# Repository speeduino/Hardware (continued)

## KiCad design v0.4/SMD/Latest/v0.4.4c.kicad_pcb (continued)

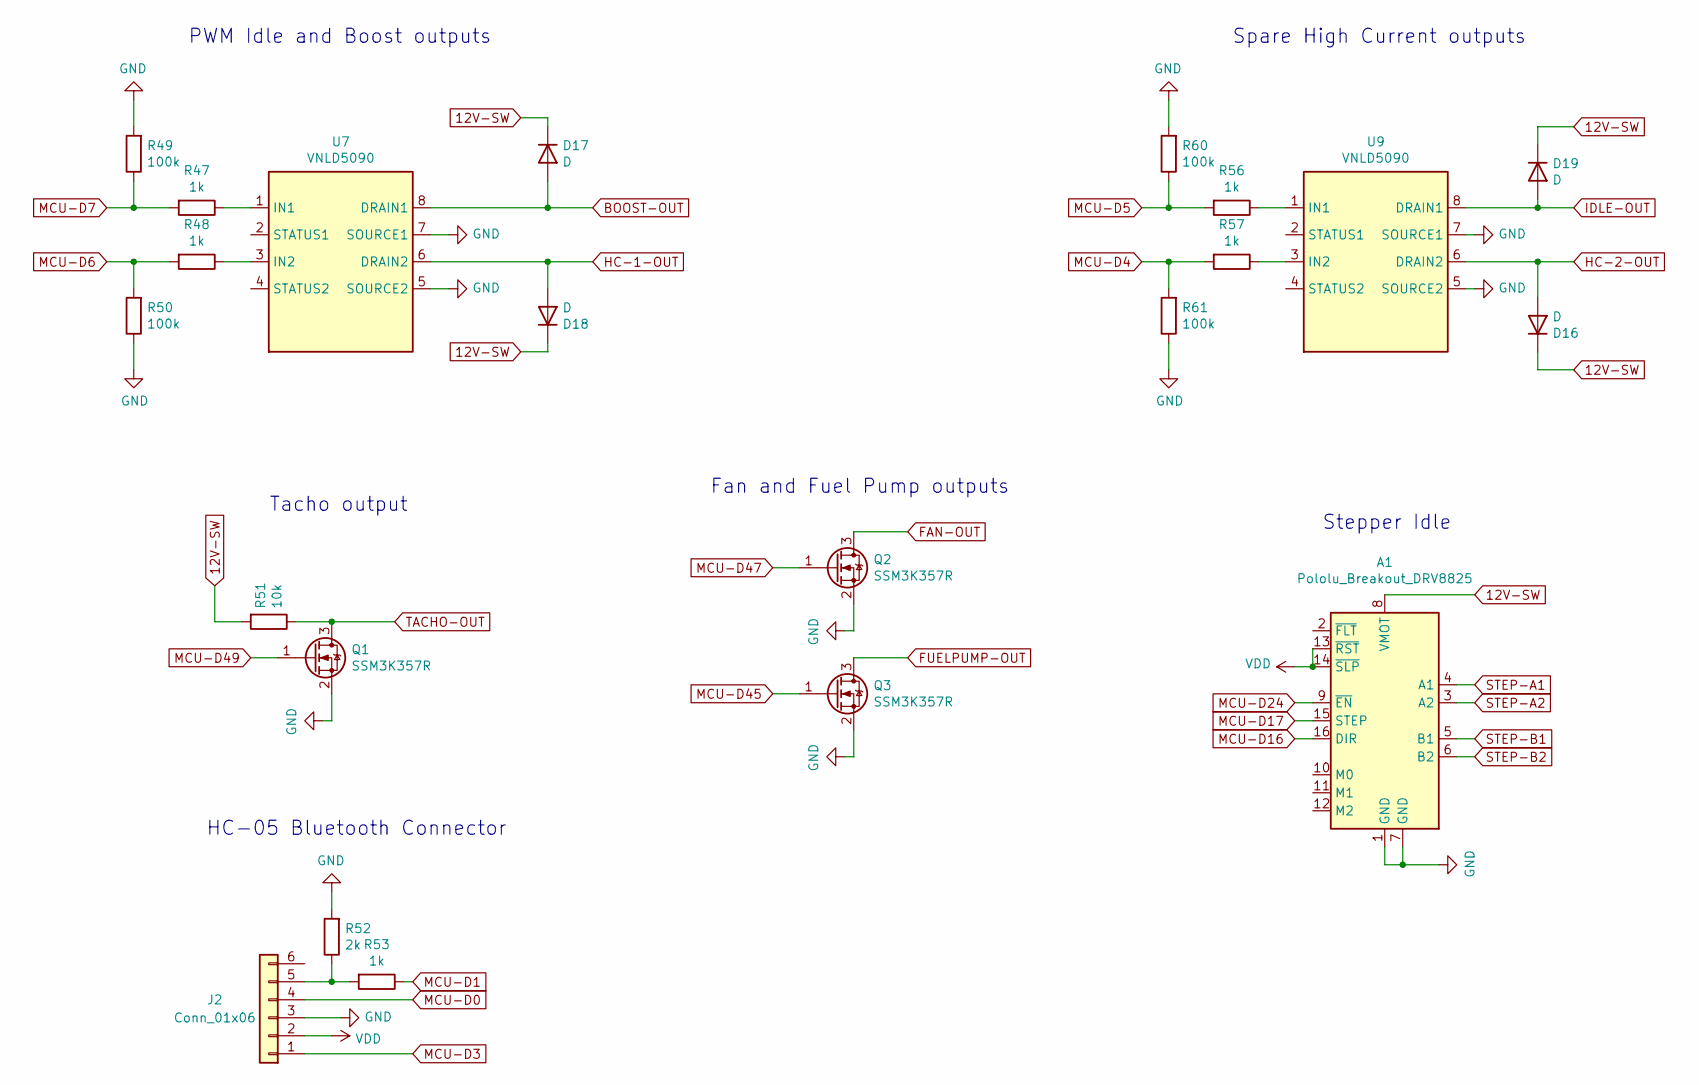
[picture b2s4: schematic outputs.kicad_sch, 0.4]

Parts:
A1: Pololu_Breakout_DRV8825; Pololu_Breakout-16_15.2x20.3mm
D16, D17, D18, D19: D; D_SOD-123F; Manufacturer_Part_Number S110FA; Digikey Part Number S110FACT-ND
J2: Conn_01x06; PinHeader_1x06_P2.54mm_Vertical
Q1, Q2, Q3: SSM3K357R; SOT-23; Manufacturer_Part_Number SSM3K357R; Digikey Part Number SSM3K357RLFCT-ND
R47, R48, R53, R56, R57: 1k; R_0805_2012Metric; Manufacturer_Part_Number RC0805FR-071KL; Digikey Part Number 311-1.00KCRCT-ND
R49, R50, R60, R61: 100k; R_0805_2012Metric; Manufacturer_Part_Number RC0805FR-07100KL; Digikey Part Number 311-100KCRCT-ND
R51: 10k; R_0805_2012Metric; Manufacturer_Part_Number RC0805JR-0710KL; Digikey Part Number 311-10KARCT-ND
R52: 2k; R_0805_2012Metric; Manufacturer_Part_Number RC0805FR-072KL; Digikey Part Number 311-2.00KCRCT-ND
U7, U9: VNLD5090; SO-8_3.9x4.9mm_P1.27mm; Manufacturer_Part_Number VNLD5090-E; Digikey Part Number 497-18682-ND

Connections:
BOOST-OUT: D17.2 (A), U7.8 (DRAIN1); also elsewhere on the board
FAN-OUT: Q2.3 (D); also elsewhere on the board
FUELPUMP-OUT: Q3.3 (D); also elsewhere on the board
GND: A1.1 (GND), A1.7 (GND), J2.3, Q1.2 (S), Q2.2 (S), Q3.2 (S), R49.2, R50.1, R52.2, R60.2, R61.1, U7.5 (SOURCE2), U7.7 (SOURCE1), U9.5 (SOURCE2), U9.7 (SOURCE1); also elsewhere on the board
HC-1-OUT: D18.2 (A), U7.6 (DRAIN2); also elsewhere on the board
HC-2-OUT: D16.2 (A), U9.6 (DRAIN2); also elsewhere on the board
IDLE-OUT: D19.2 (A), U9.8 (DRAIN1); also elsewhere on the board
MCU-D0: J2.4; also elsewhere on the board
MCU-D1: R53.1; also elsewhere on the board
MCU-D3: J2.1; also elsewhere on the board
MCU-D4: R57.2, R61.2; also elsewhere on the board
MCU-D5: R56.2, R60.1; also elsewhere on the board
MCU-D6: R48.2, R50.2; also elsewhere on the board
MCU-D7: R47.2, R49.1; also elsewhere on the board
MCU-D16: A1.16 (DIR); also elsewhere on the board
MCU-D17: A1.15 (STEP); also elsewhere on the board
MCU-D24: A1.9 (~EN); also elsewhere on the board
MCU-D45: Q3.1 (G); also elsewhere on the board
MCU-D47: Q2.1 (G); also elsewhere on the board
MCU-D49: Q1.1 (G); also elsewhere on the board
unnamed: J2.5, R52.1, R53.2
unnamed: R47.1, U7.1 (IN1)
unnamed: R48.1, U7.3 (IN2)
unnamed: R56.1, U9.1 (IN1)
unnamed: R57.1, U9.3 (IN2)
STEP-A1: A1.4 (A1); also elsewhere on the board
STEP-A2: A1.3 (A2); also elsewhere on the board
STEP-B1: A1.5 (B1); also elsewhere on the board
STEP-B2: A1.6 (B2); also elsewhere on the board
TACHO-OUT: Q1.3 (D), R51.1; also elsewhere on the board

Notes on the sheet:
Stepper Idle
HC-05 Bluetooth Connector
Spare High Current outputs
Fan and Fuel Pump outputs
PWM Idle and Boost outputs
Tacho output

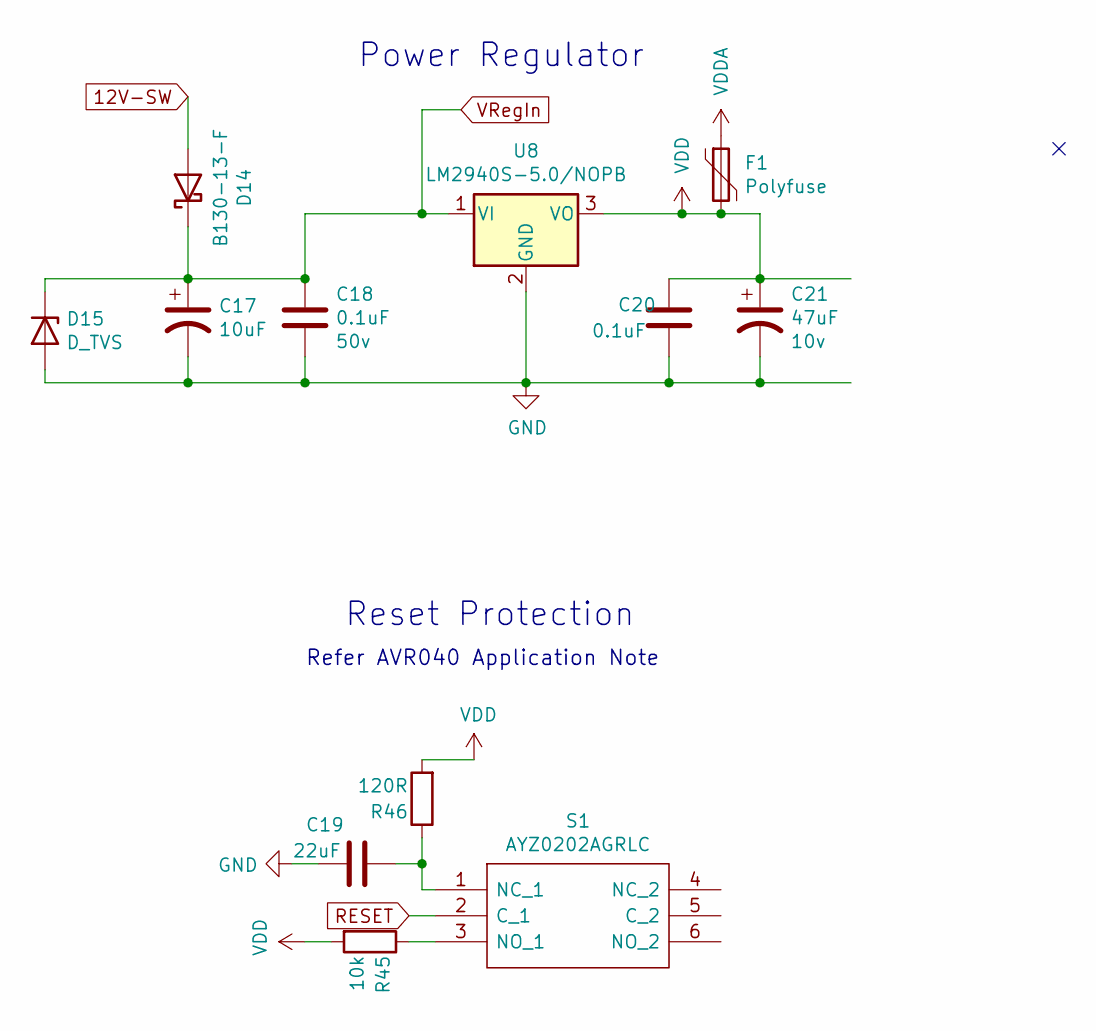
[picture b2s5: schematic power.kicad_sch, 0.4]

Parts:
C17: 10uF; CP_EIA-7343-31_Kemet-D; Voltage 35v; Manufacturer_Part_Number T491D106K050AT; Digikey Part Number 399-8361-1-ND
C18: 0.1uF; C_0805_2012Metric; Voltage 50v; Manufacturer_Part_Number CC0805KRX7R9BB104; Digikey Part Number 311-1140-1-ND
C19: 22uF; C_0805_2012Metric_Pad1.15x1.40mm_HandSolder; Manufacturer_Part_Number CL21A226KQCLRNC; Digikey Part Number 1276-6687-1-ND
C20: 0.1uF; C_0805_2012Metric; Manufacturer_Part_Number CC0805KRX7R9BB104; Digikey Part Number 311-1140-1-ND
C21: 47uF; CP_EIA-3528-21_Kemet-B; Voltage 10v; Manufacturer_Part_Number TAJB476K006RNJ; Digikey Part Number 478-1692-1-ND
D14: B130-13-F; D_SMA; Manufacturer_Part_Number B130-13-F; Digikey Part Number B130-FDICT-ND
D15: D_TVS; D_SMB; Manufacturer_Part_Number SMBJ40A-Q; Digikey Part Number SMBJ40A-QCT-ND
F1: Polyfuse; Fuse_1812_4532Metric; Manufacturer_Part_Number 0ZCC0050FF2C; Digikey Part Number 507-1361-1-ND
R45: 10k; R_0805_2012Metric; Manufacturer_Part_Number RC0805JR-0710KL; Digikey Part Number 311-10KARCT-ND
R46: 120R; R_0805_2012Metric; Manufacturer_Part_Number RC0805FR-07120RL; Digikey Part Number 311-120CRCT-ND
S1: AYZ0202AGRLC; Manufacturer_Part_Number AYZ0202AGRLC; Digikey Part Number 401-2013-1-ND
U8: LM2940S-5.0/NOPB; TO-263-3_TabPin2; Manufacturer_Part_Number LM2940S-5.0/NOPB; Digikey Part Number LM2940S-5.0/NOPB-ND

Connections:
GND: C17.2, C18.2, C19.2, C20.2, C21.2, D15.2 (A), U8.2 (GND); also elsewhere on the board
unnamed: C19.1, R46.1, S1.1 (NC_1)
unnamed: R45.1, S1.3 (NO_1)
RESET: S1.2 (C_1); also elsewhere on the board
VDDA: F1.1; also elsewhere on the board

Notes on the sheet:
Refer AVR040 Application Note
Reset Protection
Power Regulator

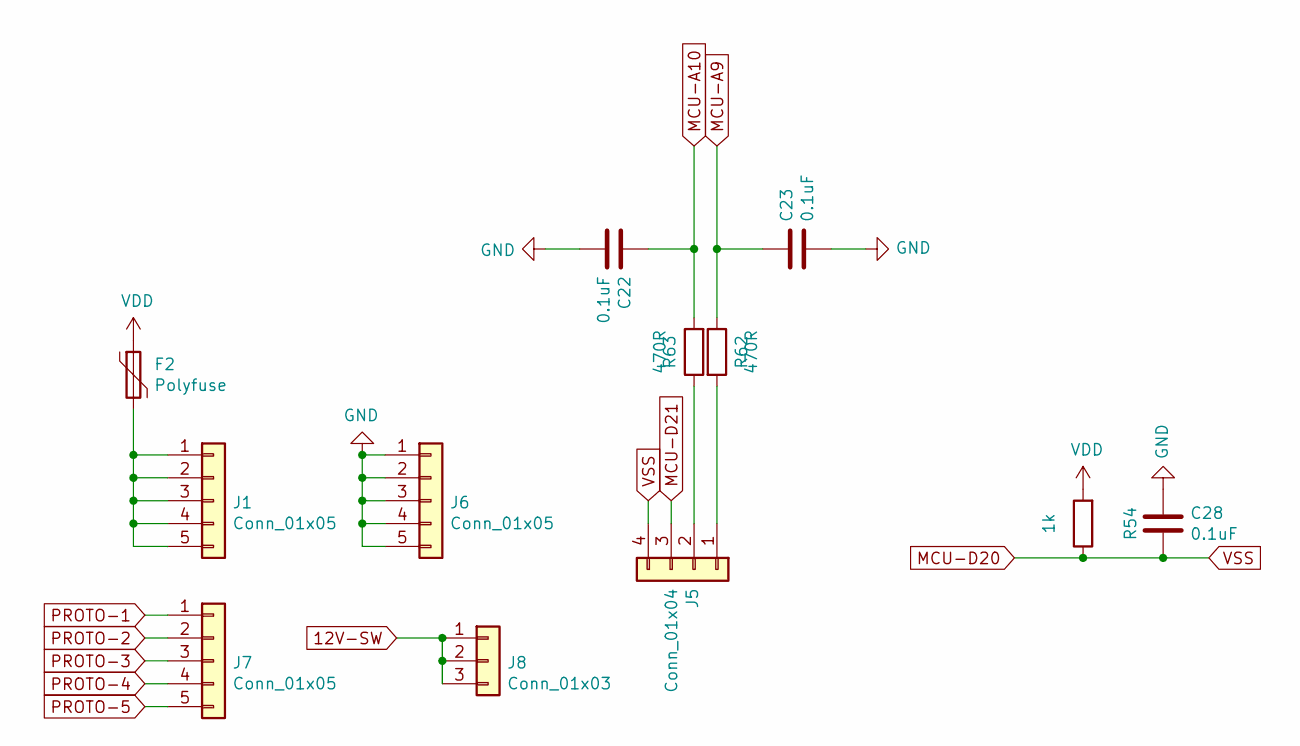
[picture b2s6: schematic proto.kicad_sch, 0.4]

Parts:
C22, C23, C28: 0.1uF; C_0805_2012Metric; Manufacturer_Part_Number CC0805KRX7R9BB104; Digikey Part Number 311-1140-1-ND
F2: Polyfuse; Fuse_1812_4532Metric; Manufacturer_Part_Number 0ZCC0050FF2C; Digikey Part Number 507-1361-1-ND
J1, J6, J7: Conn_01x05; PinHeader_1x05_P2.54mm_Vertical
J5: Conn_01x04; PinHeader_1x04_P2.54mm_Vertical
J8: Conn_01x03; PinHeader_1x03_P2.54mm_Vertical
R54: 1k; R_0805_2012Metric; Manufacturer_Part_Number RC0805FR-071KL; Digikey Part Number 311-1.00KCRCT-ND
R62, R63: 470R; R_0805_2012Metric; Manufacturer_Part_Number ERJ-6ENF4700V; Digikey Part Number P470CCT-ND

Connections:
GND: C22.2, C23.2, C28.1, J6.1, J6.2, J6.3, J6.4, J6.5; also elsewhere on the board
MCU-A9: C23.1, R63.1; also elsewhere on the board
MCU-A10: C22.1, R62.2; also elsewhere on the board
MCU-D20: C28.2, J5.4, R54.1; also elsewhere on the board
MCU-D21: J5.3; also elsewhere on the board
unnamed: F2.2, J1.1, J1.2, J1.3, J1.4, J1.5
unnamed: J5.1, R63.2
unnamed: J5.2, R62.1
PROTO-1: J7.1; also elsewhere on the board
PROTO-2: J7.2; also elsewhere on the board
PROTO-3: J7.3; also elsewhere on the board
PROTO-4: J7.4; also elsewhere on the board
PROTO-5: J7.5; also elsewhere on the board

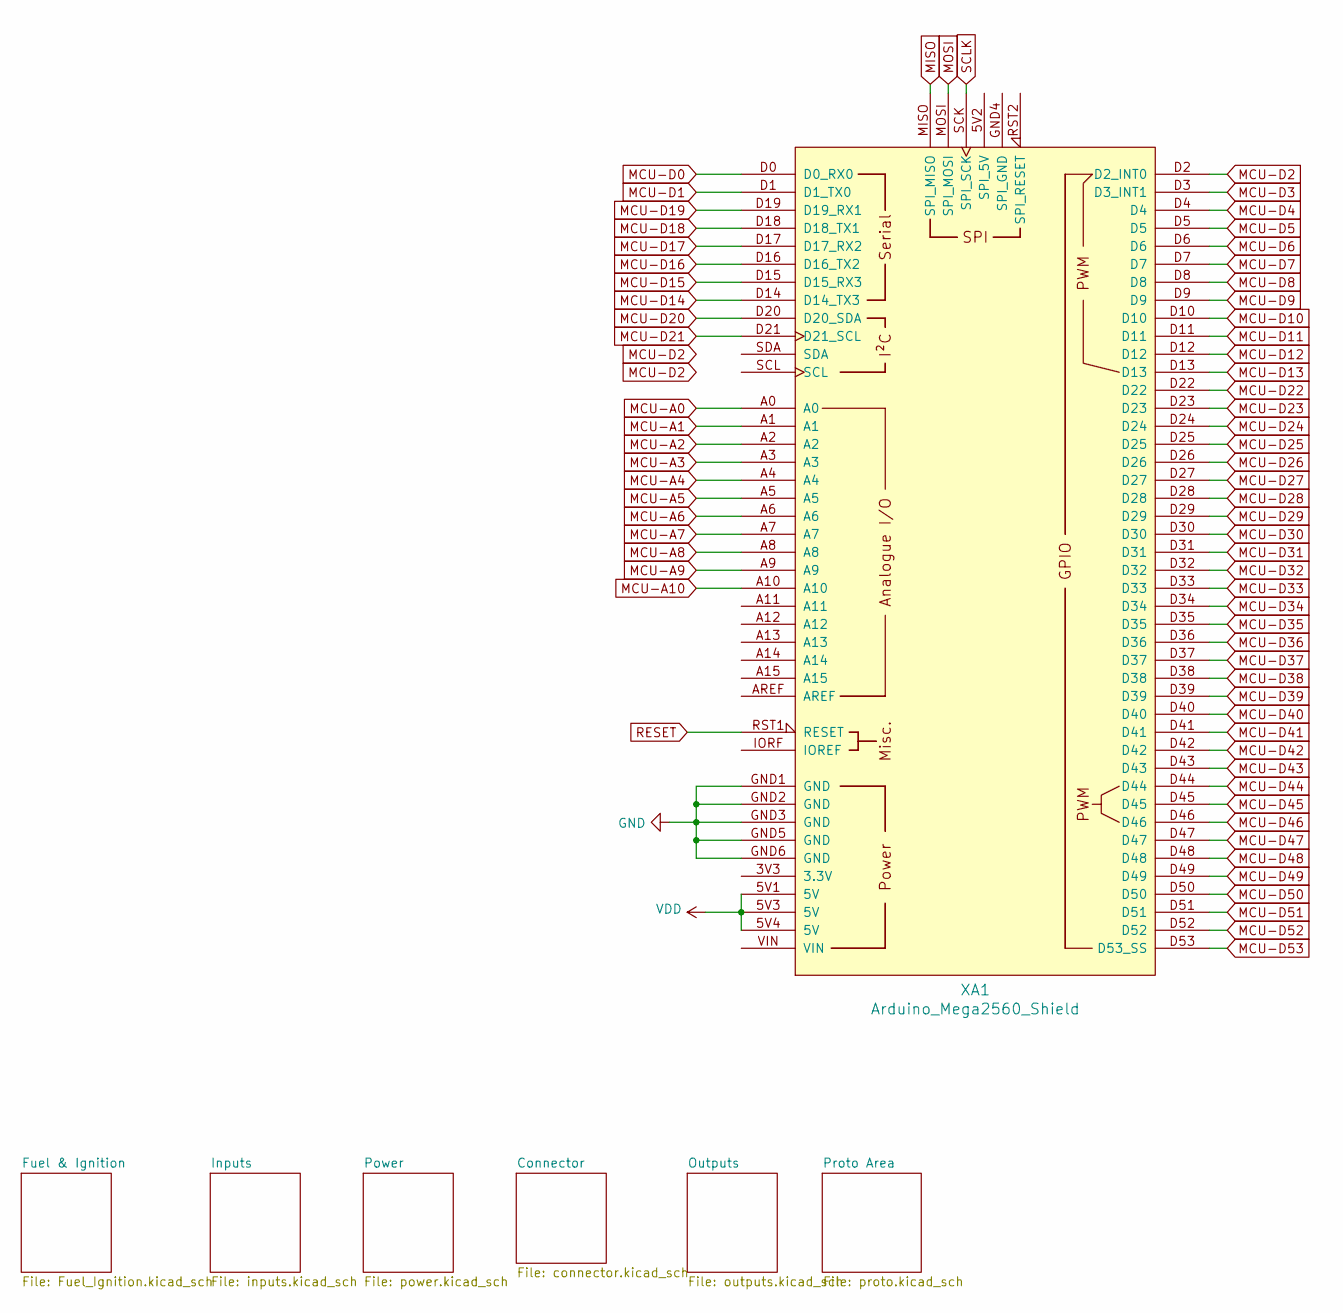
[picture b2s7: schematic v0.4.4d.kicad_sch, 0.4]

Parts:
XA1: Arduino_Mega2560_Shield; Arduino_Mega2560_Shield_IO_Only

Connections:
ADC-Clamp-1: XA1.A4; also elsewhere on the board
ADC-Clamp-2: XA1.A3; also elsewhere on the board
ADC-Clamp-3: XA1.A1; also elsewhere on the board
ADC-Clamp-4: XA1.A2; also elsewhere on the board
ADC-Clamp-5: XA1.A0; also elsewhere on the board
ADC-Clamp-6: XA1.A8; also elsewhere on the board
ADC-Clamp-8: XA1.D18 (D18_TX1); also elsewhere on the board
ADC-Clamp-9: XA1.D19 (D19_RX1); also elsewhere on the board
ADC-Clamp-10: XA1.D2 (D2_INT0); also elsewhere on the board
ADC-Clamp-13: XA1.D51; also elsewhere on the board
GND: XA1.GND1 (GND), XA1.GND2 (GND), XA1.GND3 (GND), XA1.GND5 (GND), XA1.GND6 (GND); also elsewhere on the board
MCU-A5: XA1.A5; also elsewhere on the board
MCU-A6: XA1.A6
MCU-A7: XA1.A7
MCU-A9: XA1.A9; also elsewhere on the board
MCU-A10: XA1.A10; also elsewhere on the board
MCU-D0: XA1.D0 (D0_RX0); also elsewhere on the board
MCU-D1: XA1.D1 (D1_TX0); also elsewhere on the board
MCU-D3: XA1.D3 (D3_INT1); also elsewhere on the board
MCU-D4: XA1.D4; also elsewhere on the board
MCU-D5: XA1.D5; also elsewhere on the board
MCU-D6: XA1.D6; also elsewhere on the board
MCU-D7: XA1.D7; also elsewhere on the board
MCU-D8: XA1.D8; also elsewhere on the board
MCU-D9: XA1.D9; also elsewhere on the board
MCU-D10: XA1.D10; also elsewhere on the board
MCU-D11: XA1.D11; also elsewhere on the board
MCU-D12: XA1.D12
MCU-D13: XA1.D13
MCU-D14: XA1.D14 (D14_TX3)
MCU-D15: XA1.D15 (D15_RX3)
MCU-D16: XA1.D16 (D16_TX2); also elsewhere on the board
MCU-D17: XA1.D17 (D17_RX2); also elsewhere on the board
MCU-D20: XA1.D20 (D20_SDA); also elsewhere on the board
MCU-D21: XA1.D21 (D21_SCL); also elsewhere on the board
MCU-D22: XA1.D22
MCU-D23: XA1.D23
MCU-D24: XA1.D24; also elsewhere on the board
MCU-D25: XA1.D25
MCU-D26: XA1.D26
MCU-D27: XA1.D27
MCU-D28: XA1.D28
MCU-D29: XA1.D29
MCU-D30: XA1.D30
MCU-D31: XA1.D31
MCU-D32: XA1.D32
MCU-D33: XA1.D33
MCU-D34: XA1.D34
MCU-D35: XA1.D35
MCU-D36: XA1.D36
MCU-D37: XA1.D37
MCU-D38: XA1.D38; also elsewhere on the board
MCU-D39: XA1.D39
MCU-D40: XA1.D40; also elsewhere on the board
MCU-D41: XA1.D41
MCU-D42: XA1.D42
MCU-D43: XA1.D43
MCU-D44: XA1.D44
MCU-D45: XA1.D45; also elsewhere on the board
MCU-D46: XA1.D46
MCU-D47: XA1.D47; also elsewhere on the board
MCU-D48: XA1.D48
MCU-D49: XA1.D49; also elsewhere on the board
MCU-D50: XA1.D50; also elsewhere on the board
MCU-D52: XA1.D52; also elsewhere on the board
MCU-D53: XA1.D53 (D53_SS)
RESET: XA1.RST1 (RESET); also elsewhere on the board

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
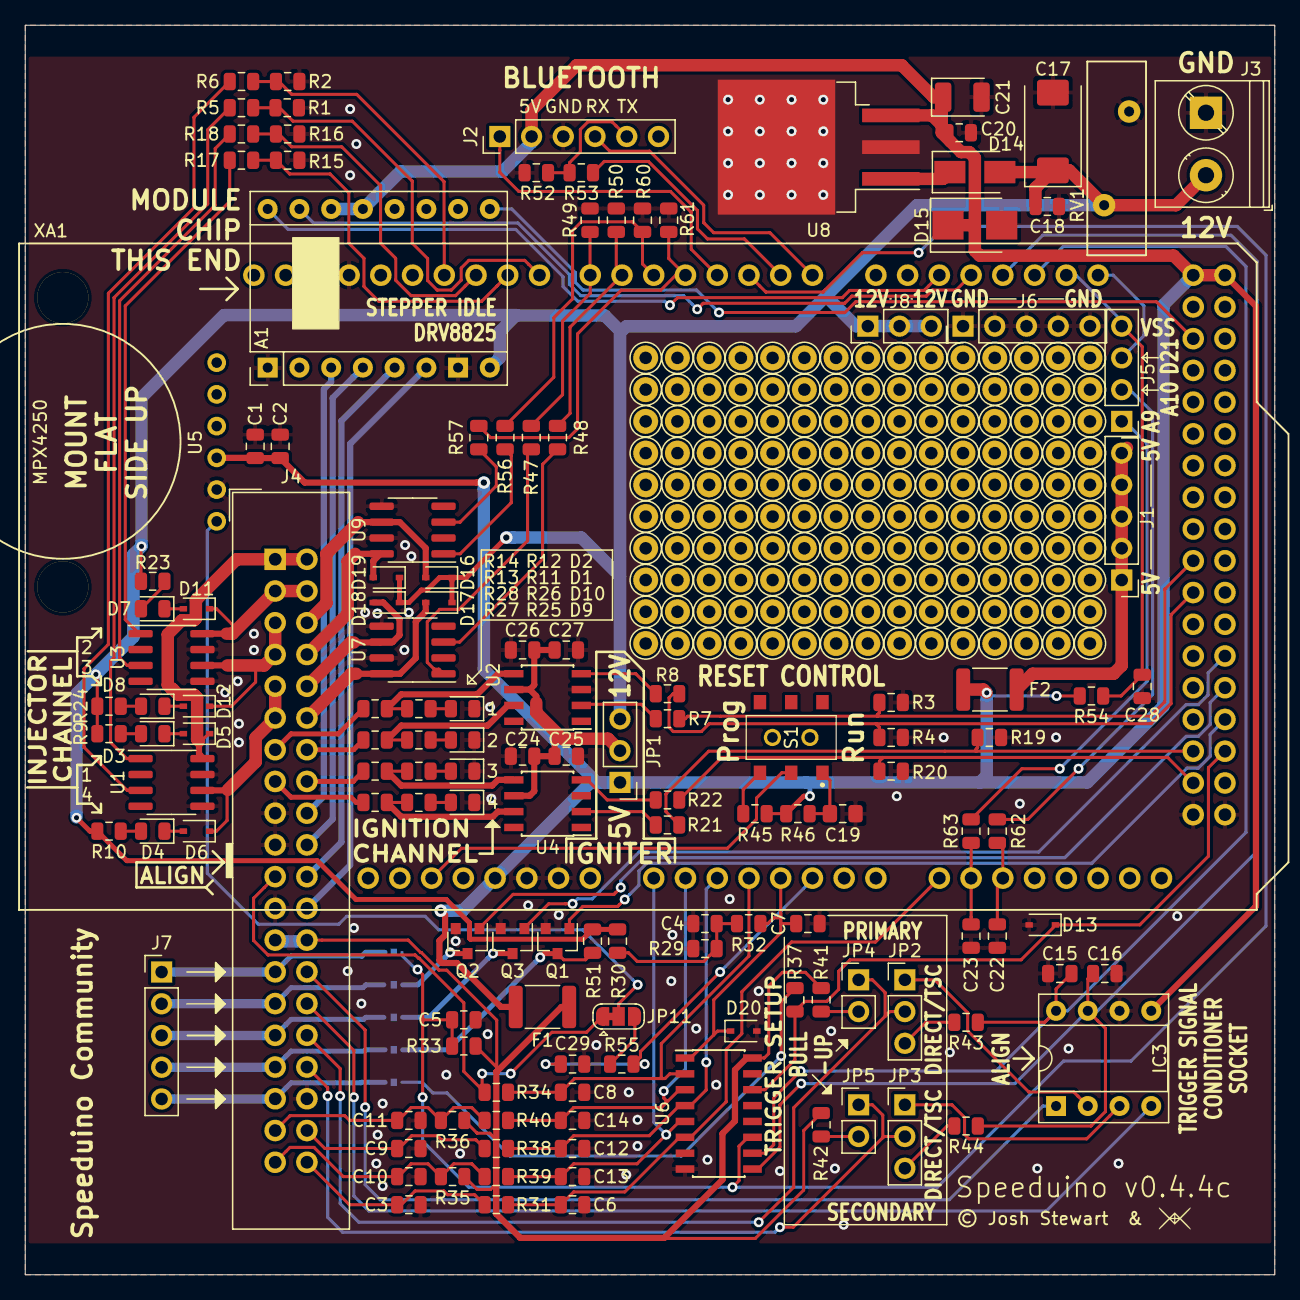
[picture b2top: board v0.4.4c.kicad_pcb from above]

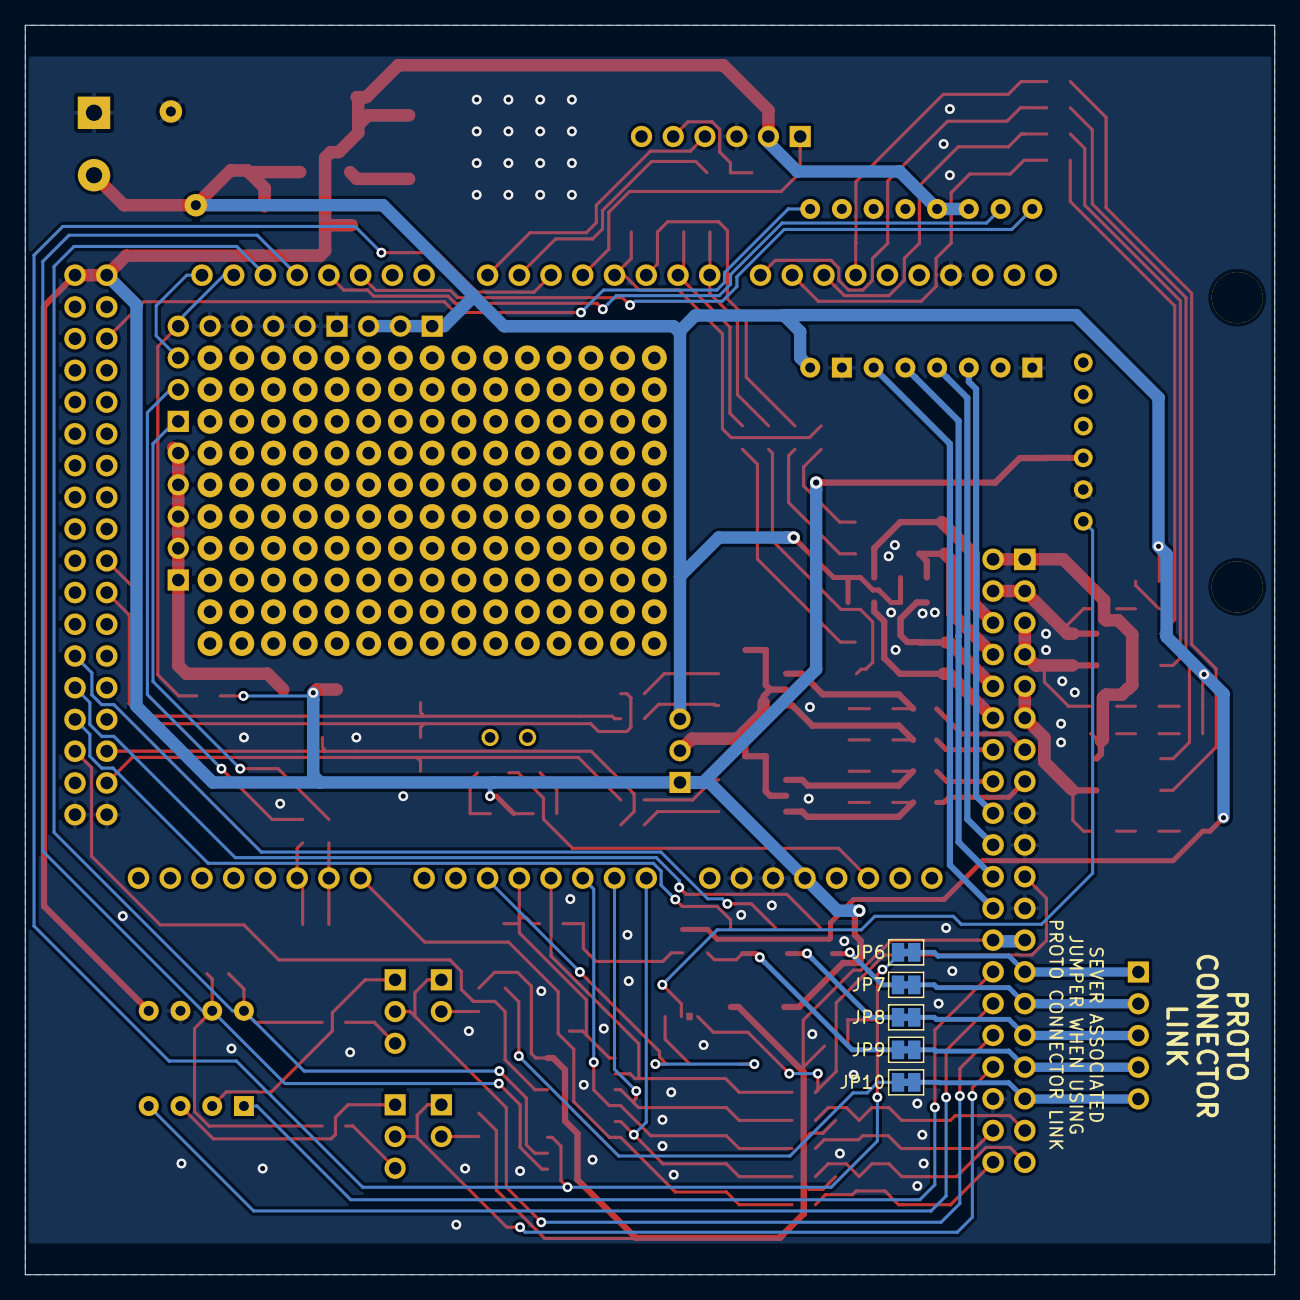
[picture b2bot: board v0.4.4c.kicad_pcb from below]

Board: 2 copper layers, 100.0 x 100.0 mm, 148 parts (5 on the bottom side), 120 nets.

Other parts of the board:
RV1: Varistor; RV_Disc_D15.5mm_W4.7mm_P7.5mm

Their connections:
GND: RV1.2; also elsewhere on the board

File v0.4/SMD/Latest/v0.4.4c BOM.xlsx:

Reference | Quantity | Value | Footprint | Manufacturer_Name | Manufacturer_Part_Number | URL
C1 C15 | 2 | 0.01uF | Capacitor_SMD:C_0805_2012Metric | Yageo | CC0805KRX7R9BB103 | https://www.digikey.com/product-detail/en/yageo/CC0805KRX7R9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
C17 | 1 | 10uF | Capacitor_Tantalum_SMD:CP_EIA-7343-31_Kemet-D | Kemet | T491D106K050AT | https://www.digikey.com/product-detail/en/kemet/T491D106K050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
C19 | 1 | 22uF | Capacitor_SMD:C_0805_2012Metric_Pad1.15x1.40mm_HandSolder | Samsung | CL21A226KQCLRNC | https://www.digikey.com.au/product-detail/en/samsung-electro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
C21 | 1 | 47uF | Capacitor_Tantalum_SMD:CP_EIA-3528-21_Kemet-B | AVX | TAJB476K006RNJ | https://www.digikey.com/product-detail/en/avx-corporation/TA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
C24 C26 C3 C9 C10 C11 C4 C16 C18 C20 C23 C22 C28 | 13 | 0.1uF | Capacitor_SMD:C_0805_2012Metric | Yageo | CC0805KRX7R9BB104 | https://www.digikey.com.au/product-detail/en/yageo/CC0805KRX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
C25 C27 C2 | 3 | 1uF | Capacitor_SMD:C_0805_2012Metric | Yageo | CC0805KKX7R7BB105 | https://www.digikey.com/product-detail/en/yageo/CC0805KKX7R7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
C6 C12 C13 C14 C7 C5 | 6 | 0.22uF | Capacitor_SMD:C_0805_2012Metric | Samsung | CL21B224KOCNNNC | https://www.digikey.com/product-detail/en/samsung-electro-me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
C8 C29 | 2 | 470pf | Capacitor_SMD:C_0805_2012Metric | Yageo | CC0805KRX7R9BB471 | https://www.digikey.com/product-detail/en/yageo/CC0805KRX7R9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
D12 D11 D5 D6 D18 D17 D19 D16 | 8 | D | Diode_SMD:D_SOD-323 | MCC | 1N4448WX-TP | https://www.digikey.com/product-detail/en/micro-commercial-c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
D13 D20 | 2 | D_Zener | Diode_SMD:D_SOD-323 | On Semi | MM3Z5V1ST1G | https://www.digikey.com/product-detail/en/on-semiconductor/M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
D14 | 1 | B130-13-F | Diode_SMD:D_SMA | Diodes Inc | B130-13-F | https://www.digikey.com.au/product-detail/en/diodes-incorpor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
D15 | 1 | 1SMB5919BT3G | Diode_SMD:D_SMB | On Semi | 1SMB5919BT3G | https://www.digikey.com.au/product-detail/en/on-semiconducto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
D4 D3 D8 D7 D1 D2 D9 D10 | 8 | LED | LED_SMD:LED_0805_2012Metric | Osram | LH R974-LP-1 | https://www.digikey.com/product-detail/en/osram-opto-semicon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
F1 F2 | 2 | Polyfuse | Fuse:Fuse_1812_4532Metric | Bel Fuse | 0ZCC0050FF2C | https://www.digikey.com.au/product-detail/en/bel-fuse-inc/0Z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
IC3 | 2 | Trig Cond Socket | Package_DIP:DIP-8_W7.62mm_Socket | Sullins Connector Solutions | PPTC041LFBN-RC | https://www.digikey.com.au/product-detail/en/sullins-connect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
J3 | 1 | Conn_01x02 | TerminalBlock_Phoenix:TerminalBlock_Phoenix_PT-1,5-2-5.0-H_1x02_P5.00mm_Horizon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 | TE | 282836-2 | https://www.digikey.com.au/product-detail/en/te-connectivity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
J4 | 1 | Conn_02x20_Counter_Clockwise | Connector_IDC:IDC-Header_2x20_P2.54mm_Vertical | CNC Tech | 571-5103308-8 | https://www.digikey.com.au/products/en?keywords=1175-1614-ND
JP1 | 1 | Ignition Voltage | Connector_PinHeader_2.54mm:PinHeader_1x03_P2.54mm_Vertical | Harwin Inc | M20-9990345 | https://www.digikey.com.au/products/en?keywords=M20-9990345
JP2 JP3 | 2 | VR-HALL | Connector_PinHeader_2.54mm:PinHeader_1x03_P2.54mm_Vertical | Harwin Inc | M20-9990345 | https://www.digikey.com.au/products/en?keywords=M20-9990345
JP5 JP4 | 2 | PULL-UP | Connector_PinHeader_2.54mm:PinHeader_1x02_P2.54mm_Vertical | Harwin Inc | M20-9990245 | https://www.digikey.com.au/products/en?keywords=M20-9990245
Q1 Q3 Q2 | 3 | SSM3K357R | Package_TO_SOT_SMD:SOT-23 | Toshiba | SSM3K357R | https://www.digikey.com.au/product-detail/en/toshiba-semicon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
R1 R2 R15 R16 R3 R4 R19 R20 R50 R49 R61 R60 | 12 | 100k | Resistor_SMD:R_0805_2012Metric | Yageo | RC0805FR-07100KL | https://www.digikey.com/product-detail/en/yageo/RC0805FR-071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
R10 R9 R24 R23 R11 R12 R25 R26 R33 | 9 | 2.4k | Resistor_SMD:R_0805_2012Metric | Yageo | RC0805FR-072K4L | https://www.digikey.com/product-detail/en/yageo/RC0805FR-072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
R13 R14 R27 R28 | 4 | 10R | Resistor_SMD:R_0805_2012Metric | Yageo | RC0805FR-0710RL | https://www.digikey.com/product-detail/en/yageo/RC0805FR-071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
R30 | 1 | 3.9k | Resistor_SMD:R_0805_2012Metric | Yageo | RC0805FR-073K9L | https://www.digikey.com/product-detail/en/yageo/RC0805FR-073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
R34 R31 R38 R39 R40 R32 R55 R63 R62 | 9 | 470R | Resistor_SMD:R_0805_2012Metric | Panasonic | ERJ-6ENF4700V | https://www.digikey.com/product-detail/en/panasonic-electron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
R35 R36 | 2 | 2.49k | Resistor_SMD:R_0805_2012Metric | Yageo | RT0805BRD072K49L | https://www.digikey.com/product-detail/en/yageo/RT0805BRD072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
R43 R44 | 2 | 220R | Resistor_SMD:R_0805_2012Metric | Yageo | RC0805FR-07220RL | https://www.digikey.com/product-detail/en/yageo/RC0805FR-072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
R45 R51 | 2 | 10k | Resistor_SMD:R_0805_2012Metric | Yageo | RC0805JR-0710KL | https://www.digikey.com/product-detail/en/yageo/RC0805JR-071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
R46 | 1 | 120R | Resistor_SMD:R_0805_2012Metric | Yageo | RC0805FR-07120RL | https://www.digikey.com/product-detail/en/yageo/RC0805FR-071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
R5 R6 R17 R18 R7 R8 R21 R22 R29 R37 R41 R42 R47 R48 R56 R57 R53 R54 | 18 | 1k | Resistor_SMD:R_0805_2012Metric | Yageo | RC0805FR-071KL | https://www.digikey.com/product-detail/en/yageo/RC0805FR-071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
R52 | 1 | 2k | Resistor_SMD:R_0805_2012Metric | Yageo | RC0805FR-072KL | https://www.digikey.com/product-detail/en/yageo/RC0805FR-072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
RV1 | 1 | Varistor | Varistor:RV_Disc_D15.5mm_W4.7mm_P7.5mm | Bournes Inc | MOV-14D220K | https://www.digikey.com.au/product-detail/en/bourns-inc/MOV-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
S1 | 1 | AYZ0202AGRLC | Misc:AYZ0202AGRLC | C & K COMPONENTS | AYZ0202AGRLC | https://www.digikey.com.au/product-detail/en/c-k/AYZ0202AGRL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
U1 U3 U7 U9 | 4 | VNLD5090 | Package_SO:SOIC-8_3.9x4.9mm_P1.27mm | STMicro | VNLD5090-E | https://www.digikey.com.au/products/en?keywords=VNLD5090-E
U2 U4 | 2 | TC4424A | Package_SO:SOIC-8_3.9x4.9mm_P1.27mm | Microchip | TC4424AVOA | https://www.digikey.com/product-detail/en/microchip-technolo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
U5 | 1 | MPX4250 | Misc:MPX4250 | NXP | MPX4250AP | https://www.digikey.com.au/product-detail/en/nxp-usa-inc/MPX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
U6 | 1 | SP720 | Package_SO:SOIC-16_3.9x9.9mm_P1.27mm | Littelfuse | SP720ABTG | https://www.digikey.com/product-detail/en/littelfuse-inc/SP7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
U8 | 1 | LM2940S-5.0/NOPB | Package_TO_SOT_SMD:TO-263-3_TabPin2 | TI | LM2940S-5.0/NOPB | https://www.digikey.com.au/products/en?keywords=LM2940S-5.0%2FNOPB
XA1 | 4 | Arduino_Mega2560 header pins | CONN HEADER .100" SNGL STR 40POS | Sullins Connector Solutions | PREC040SAAN-RC | https://www.digikey.com.au/products/en?keywords=S1012EC-40-ND | Pins on underside of board
